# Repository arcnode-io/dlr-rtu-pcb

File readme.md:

# DLR RTU PCB 🌡️⚡

> Single-PCB CM4 carrier for a solar-powered, cellular-connected RTU — mounts to a transmission tower cross-arm, integrates SoM + cellular modem + IEEE 738 sensor suite + solar/LiFePO4 power management. Feeds [`dlr-rtu-firmware`](https://gitlab.com/arcnode-io/dlr-rtu-firmware).

Solar-powered remote terminal unit (RTU) deployed unattended on transmission tower cross-arms. A ~20W solar panel and ~50Wh LiFePO4 battery keep the CM4 running indefinitely with cellular PSM idle. A soldered Quectel BG770A (LTE Cat-M1) publishes sensor data and dynamic ratings to the MQTT broker — no site WiFi or wired backhaul required. The unit is designed for 30-year conductor-adjacent deployment with no scheduled maintenance.

~100x80mm 4-layer industrial carrier. Raspberry Pi CM4 (DF40 dual-connector) + Quectel BG770A LCC + FLIR Lepton 3.5 (SPI) + DHT22 (GPIO) + SI1145 (I2C) + YL-83 (analog via ADS1115). MPPT charger from PV input, LiFePO4 BMS, buck for 5V SoM rail, AP2112K LDO for 3.3V analog front-end. Conformal coated, IP55 when potted in field enclosure.

## System Context

```plantuml
rectangle transmission_tower {
  rectangle field_enclosure {
    rectangle dlr_carrier {
      rectangle cm4_som
      rectangle cellular_module
      rectangle sensors
      rectangle power_mgmt
    }
  }
  rectangle solar_panel
  rectangle lifepo4_battery
  rectangle conductor
}

queue mqtt_broker
rectangle dispatch_api

solar_panel -d- power_mgmt: PV input
power_mgmt -l- lifepo4_battery: charge / discharge
power_mgmt -d- cm4_som: 5V / 3V3
conductor -u- sensors: thermal view\n(FLIR Lepton)
sensors -r- cm4_som: SPI / I2C / GPIO
cm4_som -r- cellular_module: UART + USB2
cellular_module -r- mqtt_broker: LTE Cat-M1
mqtt_broker -r- dispatch_api: dynamic line rating\n(utility/dlr/...)
```

The carrier is the physical sensing + edge-compute layer of the DLR feedback loop. Every measurement flows through the IEEE 738 calculation in [`dlr-rtu-firmware`](https://gitlab.com/arcnode-io/dlr-rtu-firmware), which publishes the resulting dynamic line rating for `mock-derms-dispatch-api`'s DER curtailment trigger.

## Board Spec

```mermaid
graph LR
    SOLAR["Solar Panel<br/>~20W 12V"] --> MPPT["BQ24650 MPPT<br/>+ 2x DMN4035L"]
    MPPT --> BAT["LiFePO4 4S<br/>~50Wh + BMS"]
    BAT --> BUCK["Buck<br/>5V 3A"]
    BUCK --> CM4["CM4 SoM<br/>DF40 x2"]
    BUCK --> BG["Quectel BG770A<br/>Cat-M1 LCC"]
    BUCK --> LDO["AP2112K<br/>3.3V LDO"]
    LDO --> ADC["ADS1115<br/>I2C 0x48"]
    LDO --> UV["SI1145<br/>I2C 0x60"]
    CM4 --> FLIR["FLIR Lepton 3.5<br/>SPI0 + GPIO25"]
    CM4 --> DHT["DHT22<br/>GPIO4"]
    CM4 --> ADC
    CM4 --> UV
    ADC --> RAIN["YL-83<br/>Analog 0-3.3V"]

    style SOLAR fill:#dc4,stroke:#333
    style MPPT fill:#a94,stroke:#333
    style BAT fill:#a94,stroke:#333
    style BUCK fill:#a94,stroke:#333
    style LDO fill:#a94,stroke:#333
    style CM4 fill:#4a9,stroke:#333,color:#fff
    style BG fill:#49a,stroke:#333,color:#fff
    style FLIR fill:#49a,stroke:#333,color:#fff
    style DHT fill:#94a,stroke:#333,color:#fff
    style ADC fill:#94a,stroke:#333,color:#fff
    style UV fill:#94a,stroke:#333,color:#fff
    style RAIN fill:#669,stroke:#333,color:#fff
```

## CM4 Pinout

```mermaid
flowchart LR
classDef default fill:transparent,stroke:#333
classDef pwr fill:#4a9,stroke:#333,color:#fff
classDef spi fill:#49a,stroke:#333,color:#fff
classDef i2c fill:#94a,stroke:#333,color:#fff
classDef gpio fill:#a94,stroke:#333,color:#fff
classDef uart fill:#a49,stroke:#333,color:#fff
classDef usb fill:#669,stroke:#333,color:#fff

subgraph cm4 ["CM4 (DF40-100)"]
  p_5v["5V_IN"]
  p_sda["GPIO2 SDA1"]
  p_scl["GPIO3 SCL1"]
  p_g4["GPIO4"]
  p_g25["GPIO25"]
  p_mosi["GPIO10 MOSI"]
  p_miso["GPIO9 MISO"]
  p_sck["GPIO11 SCLK"]
  p_ce0["GPIO8 CE0"]
  p_txd["GPIO14 TXD"]
  p_rxd["GPIO15 RXD"]
  p_usb["USB2 D+/D-"]
end

subgraph onboard ["Carrier Components"]
  flir["FLIR Lepton 3.5"]
  dht["DHT22"]
  si["SI1145"]
  ads["ADS1115"]
  yl["YL-83"]
  bg["BG770A"]
end

p_mosi --> flir
p_miso --> flir
p_sck --> flir
p_ce0 --> flir
p_g25 --> flir
p_g4 --> dht
p_sda --> si
p_scl --> si
p_sda --> ads
p_scl --> ads
ads --> yl
p_txd --> bg
p_rxd --> bg
p_usb --> bg

class p_5v pwr
class p_mosi,p_miso,p_sck,p_ce0 spi
class p_sda,p_scl i2c
class p_g4,p_g25 gpio
class p_txd,p_rxd uart
class p_usb usb
```

## Sensor Interfaces

| Sensor | Interface | CM4 Pins | Sample Rate | Measurement | Feeds IEEE 738 Variable |
|--------|-----------|----------|-------------|-------------|------------------------|
| FLIR Lepton 3.5 | SPI0 + VSYNC | GPIO 8, 9, 10, 11, 25 | 8.6 Hz (frame) | Conductor surface temp | $R_{thermal}$ |
| DHT22 | GPIO4 (1-Wire) | GPIO 4 | 0.5 Hz | Ambient temp + humidity | $T_{amb}$ |
| SI1145 | I2C (0x60) | GPIO 2, 3 | 10 Hz | UV / Visible / IR irradiance | $\Delta T_{solar}$ |
| YL-83 → ADS1115 | I2C (0x48) ch0 | GPIO 2, 3 | 860 SPS | Rain intensity (0–3.3V analog) | $\Delta T_{rain}$ |

Every sensor reading on this board maps to exactly one term in the IEEE 738 dynamic rating equation:

$$ I_{max} = \sqrt{\frac{q_c + q_r - q_s}{R_{ac}}} $$

## Anemometer Variants

Single PCB + single firmware binary. Variant lives in the **kit BOM** — sensor,
cable harness, PV panel, and battery differ per SKU. Both sensors speak
NMEA 0183 (`$..MWV`) over RS-485, so the firmware driver is talker-agnostic.

### Kit BOM

| Component | High-wind kit (`DLR-CRN-HW`) | Low-wind kit (`DLR-CRN-LW`) |
|-----------|------------------------------|------------------------------|
| PCB | `dlr-rtu-pcb-v1` (same) | `dlr-rtu-pcb-v1` (same) |
| Firmware | `dlr-rtu-firmware` (same binary) | `dlr-rtu-firmware` (same binary) |
| Sensor | Calypso ULP STD | Vaisala WMT702 |
| Sensor wire protocol | NMEA `$IIMWV` over RS-485 | NMEA `$WIMWV` over RS-485 |
| Sensor accuracy (V<2 m/s) | ±5 % + 0.2 m/s offset (1 m/s threshold) | **±0.1 m/s** (0.01 m/s threshold) |
| Sensor op temp | unspecified (consumer-grade) | -10 to +60 °C |
| Cable harness | 5 m bare-wire to M12-5P | 5 m Cannon Trident 19-way to M12-5P |
| PV panel | 20 W | **30 W** |
| Battery | 50 Wh LiFePO4 | **100 Wh LiFePO4** |
| Sticker | `HW-1.0` | `LW-1.0` |
| Kit cost (approx) | ~$650 | ~$2350 |

### When to deploy which variant

Per-site SKU pick uses NREL WIND Toolkit climatology (or customer SCADA wx
history when available). Threshold: fraction-of-year with V_w < 1 m/s
perpendicular to conductor.

| Climatology | Variant | Why |
|---|---|---|
| ≤ 15 % yr V_w < 1 m/s (ridge / coastal / open plain w/ mean ≥ 6 m/s) | high-wind | uplift slice below 1 m/s is marginal; static fallback below threshold is fine |
| > 15 % yr V_w < 1 m/s (valley / sheltered / open plain w/ mean ≤ 5 m/s) | low-wind | uplift slice is material; pay $1.7 k premium to capture it |

### Fallback policy (both variants)

When the sensor reports `void` status, times out, or has a checksum/parse
error, the driver returns `None`. The IEEE 738 layer collapses None →
`V_w = 0.0` → natural-convection-only ampacity = the conductor's static
rating. Same conservative fallback used for the icing-fallback policy.

### Variant power budget

| | High-wind | Low-wind |
|---|---|---|
| Sensor continuous draw | 1 mW | 480 mW |
| System daily energy | 29.1 Wh | 40.6 Wh |
| Winter PV harvest (worst) | 45 Wh | 67.5 Wh |
| Winter margin | 1.55× | **1.66×** |
| Battery autonomy at 0 PV | 1.58 d | **2.22 d** |

Low-wind variant's 30 W / 100 Wh upgrade absorbs the WMT702's higher draw and
restores both winter margin and 2-day autonomy.

## Power Budget

| Rail | Source | Consumer | Idle (PSM) | Typical | Peak |
|------|--------|----------|------------|---------|------|
| 5V | Buck | CM4 | 80 mA | 1400 mA | 3000 mA (boot) |
| 5V | Buck | Quectel BG770A | <1 mA | 100 mA | 250 mA (TX) |
| 5V | Buck | FLIR Lepton 3.5 | 150 mA | 150 mA | 650 mA (shutter) |
| 5V | Buck | DHT22 | 1.5 mA | 1.5 mA | 2.5 mA |
| 3.3V | AP2112K LDO | ADS1115 + SI1145 + YL-83 | 9 mA | 9 mA | 14 mA |
| | | **Total @ 5V equiv** | **240 mA** | **1660 mA** | **3920 mA** |

The 3920 mA peak is a worst-case *sum*, not a supported operating point. The LMR33630 delivers 3.375 A with worst-case silicon, so a coincident CM4-boot + Lepton-shutter + modem-TX peak browns the rail out below the CM4's 4.75 V floor — firmware sequences those loads apart (**ADR-017**, derived in `theory.ipynb` §7 and asserted in `sim/test_spice.py`). The CM4 boot peak on its own holds the rail at ~4.95 V.

Daily energy with CM4-always-on idle + 1/min sensor wake + 1/15 min cellular TX: **~29 Wh/day** (derived in `theory.ipynb`). A 50 Wh battery (90% DoD) gives ~1.6 days autonomy with no PV. A 20W panel at 2.5 sun-hours/day (winter Northeast US worst case) delivers ~45 Wh/day after MPPT η — **1.55x winter margin**, 2.5x annual avg.

That margin assumes a 120 mA CM4 idle (tuned Pi OS Lite, headless). The CM4 datasheet §5.3 quotes ~400 mA typical idle; at that figure the budget is 62.6 Wh/day and the 20 W panel does **not** carry winter (0.72x). Idle current is the single measurement that most needs a bench check before committing to the panel size.

## Environmental

| Parameter | Spec | Notes |
|-----------|------|-------|
| Operating temp | -20°C to +85°C | CM4 commercial spec; cold-start heater required below -20°C |
| Conformal coat | Dow Corning 1-2577 | Applied post-assembly, mask connectors |
| Enclosure rating | IP55 (with field enclosure) | Board alone is not rated |
| Vibration | IEC 60068-2-6 (5–500 Hz, 2g) | Transmission tower wind loading |
| Expected service life | 30 years | Matches conductor replacement cycle |
| MTBF | >200,000 hours | Derated per MIL-HDBK-217F |
| Mounting | M3 standoffs, 4-corner | Single rigid PCB — no stack |

## Fabrication Pipeline

Fully scripted — no GUI step. KiCad's "Update PCB from Schematic" is GUI-only, so `cad/drawing/sync_pcb.py` does the same job from the SKiDL netlist: it rebuilds every footprint from the library and reassigns every pad net, which is what keeps the board honest about what the schematic says.

```
 1. uv run poe notebook         → theory.ipynb: power, signal integrity, 5V transients
 2. uv run poe build            → SKiDL netlist
 3. uv run poe schematic        → hierarchical .kicad_sch (one sheet per block)
 4. uv run poe validate-model   → ERC, 0 violations (exits non-zero otherwise)
 5. uv run poe sim / cover      → pytest: hand calcs + ngspice transients

 6. uv run poe layout-asm       → the whole board flow, in order:
      build       netlist from SKiDL
      sync-asm    footprints + pad nets  <- replaces the GUI "Update PCB from Schematic"
      place-asm   positions from cad/pcb_placement.yaml
      setup-asm   4-layer stack, design rules, net classes, GND + 5V planes
      fanout-asm  escape vias for the 0.4 mm connector, assigned before routing
      route-asm   Specctra DSN -> Freerouting -> SES import -> zone fill
      stitch-asm  vias from surface pads to their plane
      validate-asm DRC, 0 violations

    ┌──────────────────────────────────────────────────────┐
    │  HUMAN: review the render, adjust pcb_placement.yaml │
    └──────────────────────────────────────────────────────┘

 7. uv run poe generate-asm     → gerbers + drill + STEP + BOM + CPL
```

### Board status

ERC is 0. DRC is clean of clearance, short, annular-ring, hole and courtyard errors —
what is left is 7 silkscreen-overlap warnings and **2 open connections** out of 457
pads, both of them ground pins on J5 (Hirose DF40, 0.4 mm pitch):

| Net | Pad | At (mm) |
|---|---|---|
| GND | J5.20 | 197.80, 94.46 |
| GND | J5.25 | 199.00, 97.54 |

Both are redundant pins — the CM4 bonds its grounds internally — so what is missing is
return-path quality at that corner of the connector, not a broken net. It is still a
DRC error, so the gerbers in `output/` stay a preview until it closes.

**Why they are open.** It is a fanout-capacity limit, not a search failure. A row of
0.6 mm escape vias needs 0.75 mm centre to centre, so on a 0.4 mm pad pitch only every
other pin gets a via in the first row. The pins that miss out have to reach a second,
deeper row — but two 0.6 mm vias 0.75 mm apart leave a 0.15 mm slot, and a 0.2 mm trace
with 0.15 mm clearance needs 0.5 mm. **Once the first row is populated the second row is
unreachable.** Via rows have to be assigned before any routing happens; a router that
picks the nearest free site per pin always finishes one slot short.

`cad/drawing/fanout.py` does that assignment: it clears the connector's fanout band and
alternates along each pad row, one pin into the inter-row gap, the next out the back, so
same-side vias land 0.8 mm apart. It places all 39 escapes on J5 with zero clearance,
short or drill violations — the geometry works.

What is *not* done is the rebuild. Run on a board that is already routed, the pass has
to clear 223 tracks and vias to own its band, and `escape_pins` rebuilds only 23 of the
35 connections that leaves open — a net regression against the 2 here. Its place is
before Freerouting, where a full-strength router does the reconnection, which is where
`poe layout-asm` now calls it. **That path has not been run end to end yet**, so the
board in this repo is still the pre-fanout one. Closing the last two means either that
full regeneration, or 0.45 / 0.25 mm vias (JLCPCB advanced tier, and the 0.13 mm
annular-ring rule would have to come down with them), or six layers.

### Toolchain

**KiCad 10 required.** The board is KiCad 10 format (`20260206`); on KiCad 9
`poe validate-asm` says DRC could not run rather than passing silently. The CI
runner gets 10.x from Flatpak. The schematic is format `20250114`, which both
versions read.

ERC is a blocking gate in CI. DRC runs and reports but does not gate yet — the two
open ground pins above are real errors; the `|| echo` comes off once they are closed.

## Layer Stack

4-layer, 1.6 mm FR4, controlled impedance (ADR-016). Applied by `cad/drawing/board_setup.py`, so a regenerated board always has the same stack.

| Layer | Use |
|-------|-----|
| F.Cu | Signal — high-speed (SPI 20MHz, USB2.0 to BG770A) |
| In1.Cu | GND plane, unbroken (reference for the USB pair and the Lepton SPI) |
| In2.Cu | 5V_RAIL plane — CM4, both LDOs and the Lepton feed off it via drops |
| B.Cu | Signal — low-speed (I2C, GPIO, UART) |

Signals are confined to F.Cu / B.Cu: the router is told the inner layers are `power` type, so nothing slices a plane. VBAT, 3V3 and 3V8 run as 0.6 mm traces (`power` net class), necked to 0.25/0.2 mm where an escape has to squeeze past a 0.4 mm-pitch pad. Every via is 0.6/0.3 mm: a 0.5/0.25 mm via would ease the DF40 fanout but leaves a 0.125 mm annular ring, under the 0.13 mm rule.

Unbroken ground plane under the Lepton is critical — SPI runs at 20 MHz and the thermal imager is noise-sensitive. USB2.0 to the BG770A is differential-routed at 90Ω matched impedance with GND directly below. Analog traces from YL-83 to ADS1115 are guard-ringed on F.Cu. Cellular antenna is 50Ω microstrip to a u.FL connector.

## Project Structure

```
├── pyproject.toml              # Dependencies and build config
├── theory.ipynb                # Power, signal integrity, 5V transient derivations
├── sim/
│   ├── constants.py            # Sourced part parameters (datasheet + edition cited)
│   ├── model.py                # Closed-form: buck current, energy, I2C/SPI/USB
│   ├── spice_bank.py           # Shared 5V output capacitor bank
│   ├── spice_ripple.py         # ngspice: open-loop switching ripple (Eq 7)
│   ├── spice_load_step.py      # ngspice: averaged current-mode boot-peak droop
│   ├── test_run.py             # Assert closed-form results match theory.ipynb
│   └── test_spice.py           # Assert ngspice results match theory.ipynb §7
├── cad/
│   ├── netlist/
│   │   ├── model.py            # Top-level SKiDL circuit (main carrier)
│   │   ├── charger.py          # Solar input + BQ24650 MPPT charger (ADR-015)
│   │   ├── power.py            # LMR33630 5V buck + AP2112K / LP5907 LDOs
│   │   ├── som.py              # CM4 DF40 connector + decoupling
│   │   ├── cellular.py         # BG770A + SIM holder + u.FL
│   │   ├── sensors.py          # FLIR (FFC), DHT22, SI1145, ADS1115, YL-83
│   │   ├── anemometer.py       # RS-485 wind sensor port (SKU-agnostic)
│   │   ├── connectors.py       # Battery + debug + USB-C commissioning
│   │   └── lepton_daughter.py  # Daughterboard SKiDL (Molex socket + FFC)
│   ├── schematic/              # Hierarchical .kicad_sch generator
│   │   ├── schematic.py        # Netlist parse, block classification, placement
│   │   ├── multi_sheet.py      # Per-block child sheets, power symbols, PWR_FLAG
│   │   ├── root_sheet.py       # Root sheet + cross-net sheet pins
│   │   └── sch_guard.py        # Fails the build on cross-net wire/pin collisions
│   ├── drawing/                # Board pipeline (system python3 — pcbnew)
│   │   ├── sync_pcb.py         # Footprints + pad nets from the netlist
│   │   ├── place_pcb.py        # Positions from pcb_placement.yaml
│   │   ├── board_setup.py      # 4-layer stack, rules, net classes, planes
│   │   ├── route_pcb.py        # DSN -> Freerouting -> SES -> fill
│   │   ├── fanout.py           # Pre-assigned escape vias for fine-pitch connectors
│   │   ├── stitch_planes.py    # Surface-pad vias into the planes
│   │   ├── close_gaps.py       # L-shaped hops across the autorouter's leftovers
│   │   ├── maze_grid.py        # Grid window shared by the escape router
│   │   ├── maze_field.py       # Analytic clearance fields (foreign copper only)
│   │   ├── maze_search.py      # Grid A*, 8-way, with via layer changes
│   │   ├── maze_escape.py      # Route + verify one connection, or tear it out again
│   │   ├── escape_pins.py      # Drives the escape router off the DRC report
│   │   ├── rip_targets.py      # Finds a stranded pin's blockers; performs the rip
│   │   └── rip_up.py           # Rip / re-route / keep-only-if-better loop
│   ├── lepton_daughter/        # Second PCB (per ADR-013) — Lepton + bracket
│   ├── assembly/               # CadQuery → GLB pipeline (build_assembly.py)
│   ├── layout_spec.yaml        # Schematic block layout
│   ├── pcb_placement.yaml      # Main-PCB component positions
│   └── drawing-sheet.kicad_wks # Title block
├── output/
│   ├── drawings/               # Schematic SVG + PDF
│   ├── gerbers/                # Fabrication files
│   └── fab/                    # BOM + CPL for assembly
└── readme.md                   # This file
```

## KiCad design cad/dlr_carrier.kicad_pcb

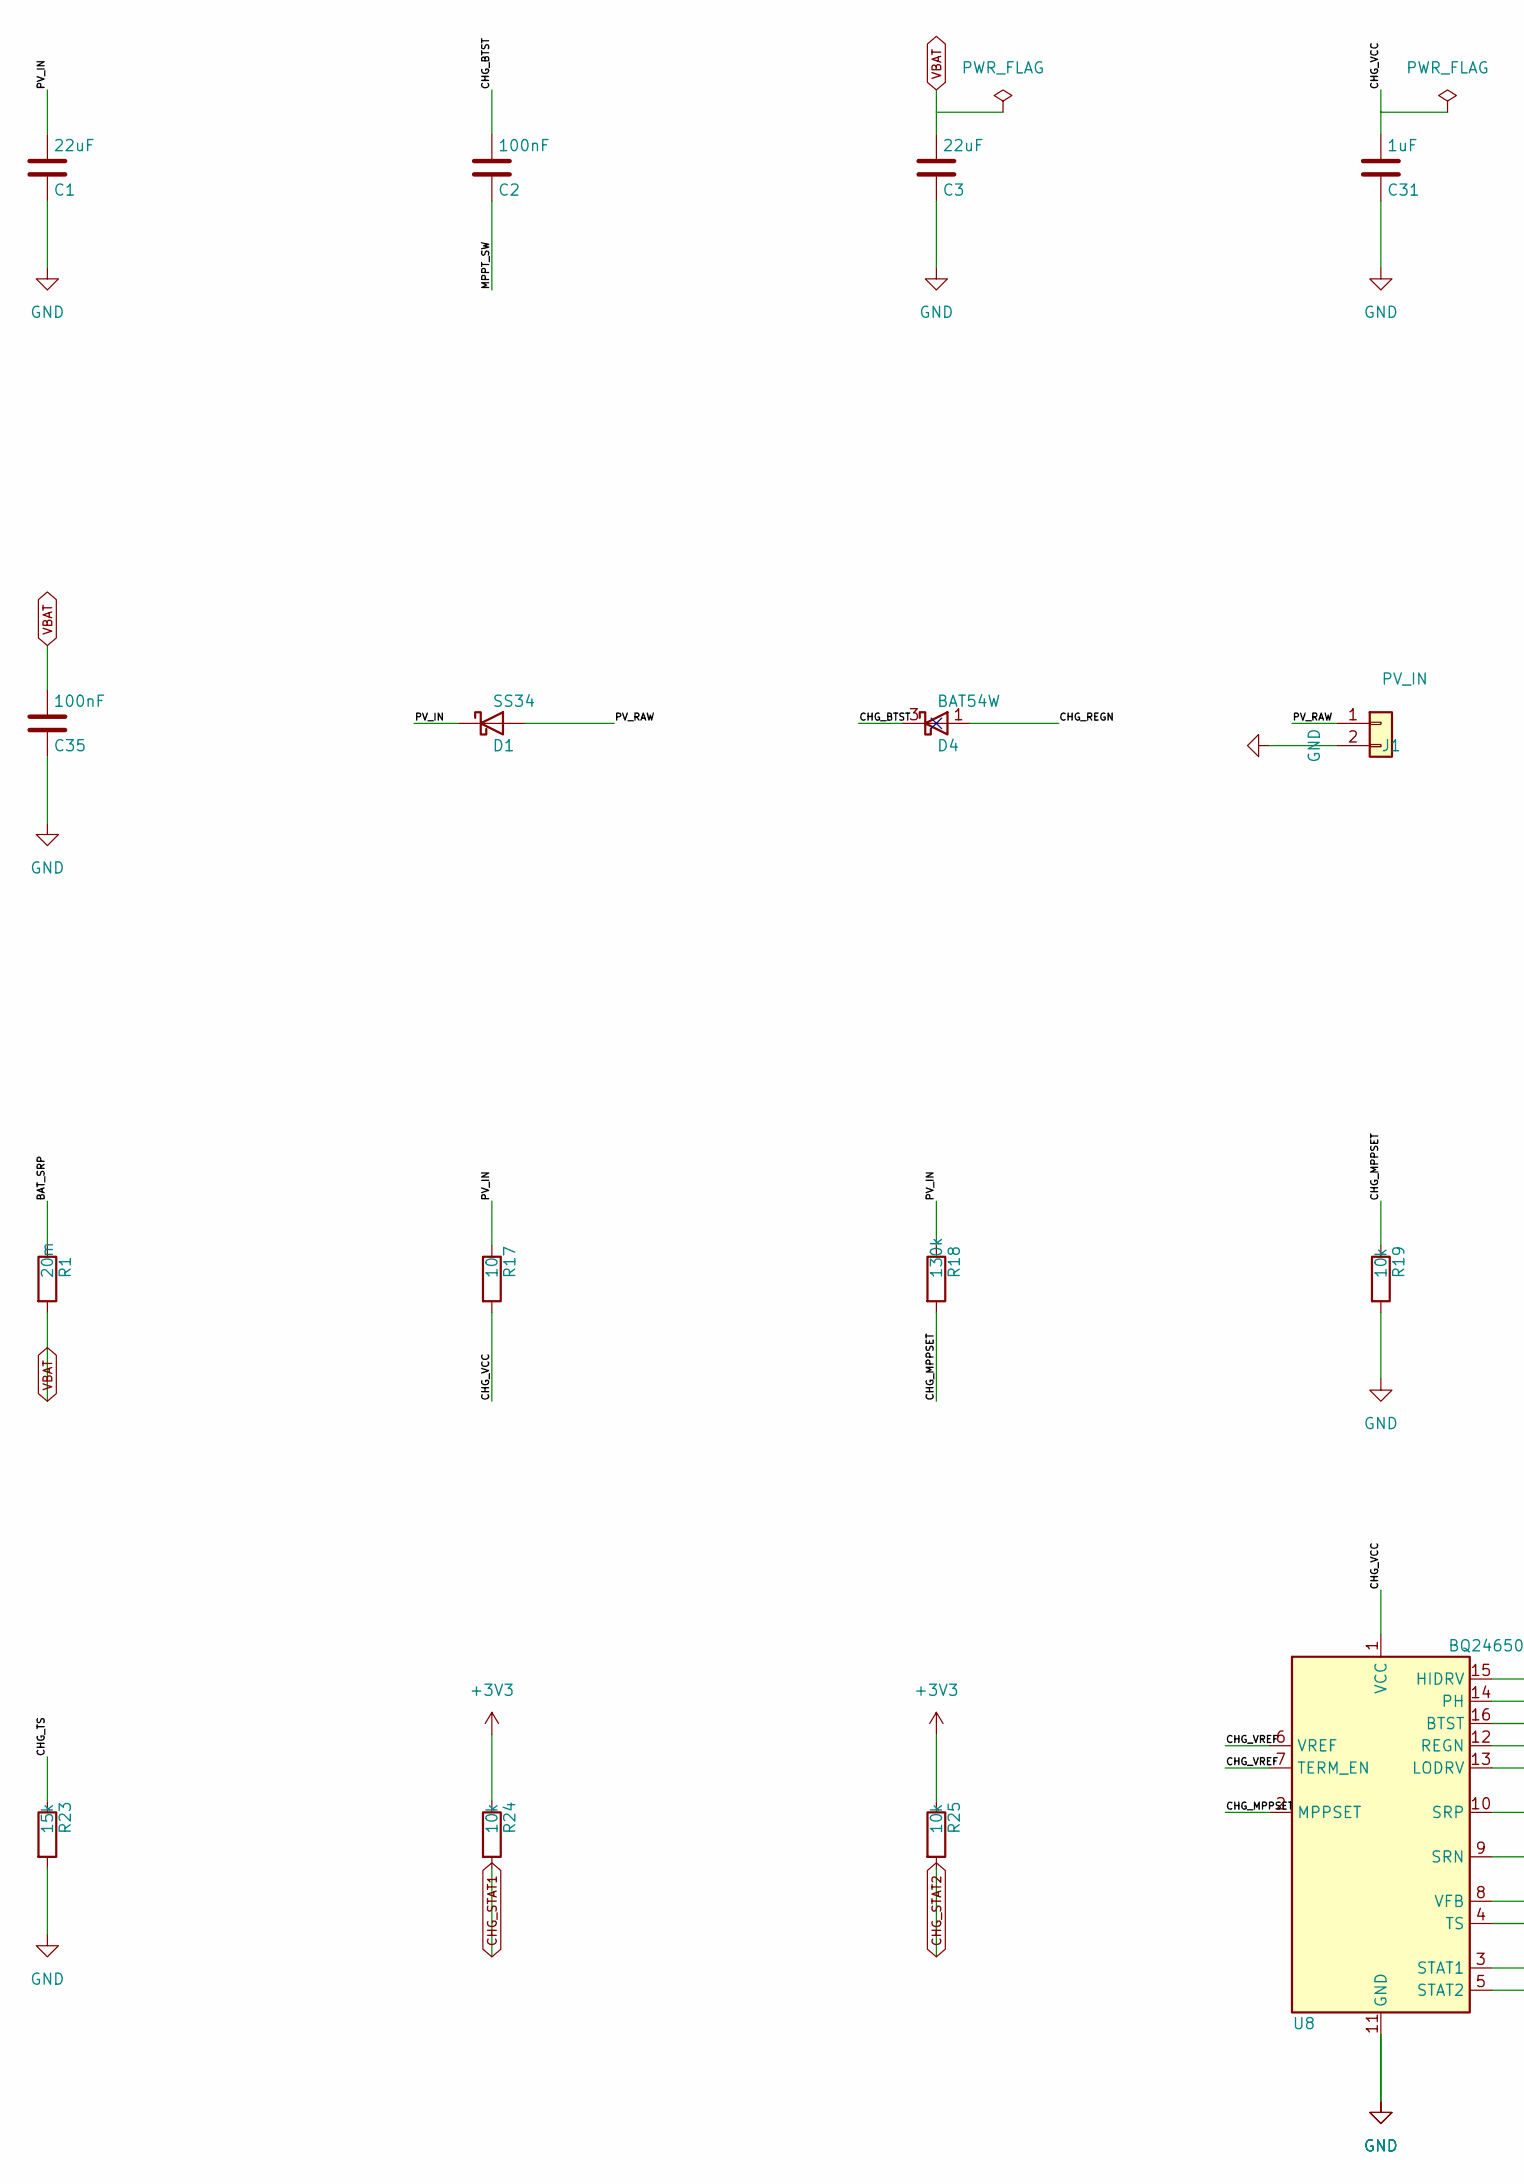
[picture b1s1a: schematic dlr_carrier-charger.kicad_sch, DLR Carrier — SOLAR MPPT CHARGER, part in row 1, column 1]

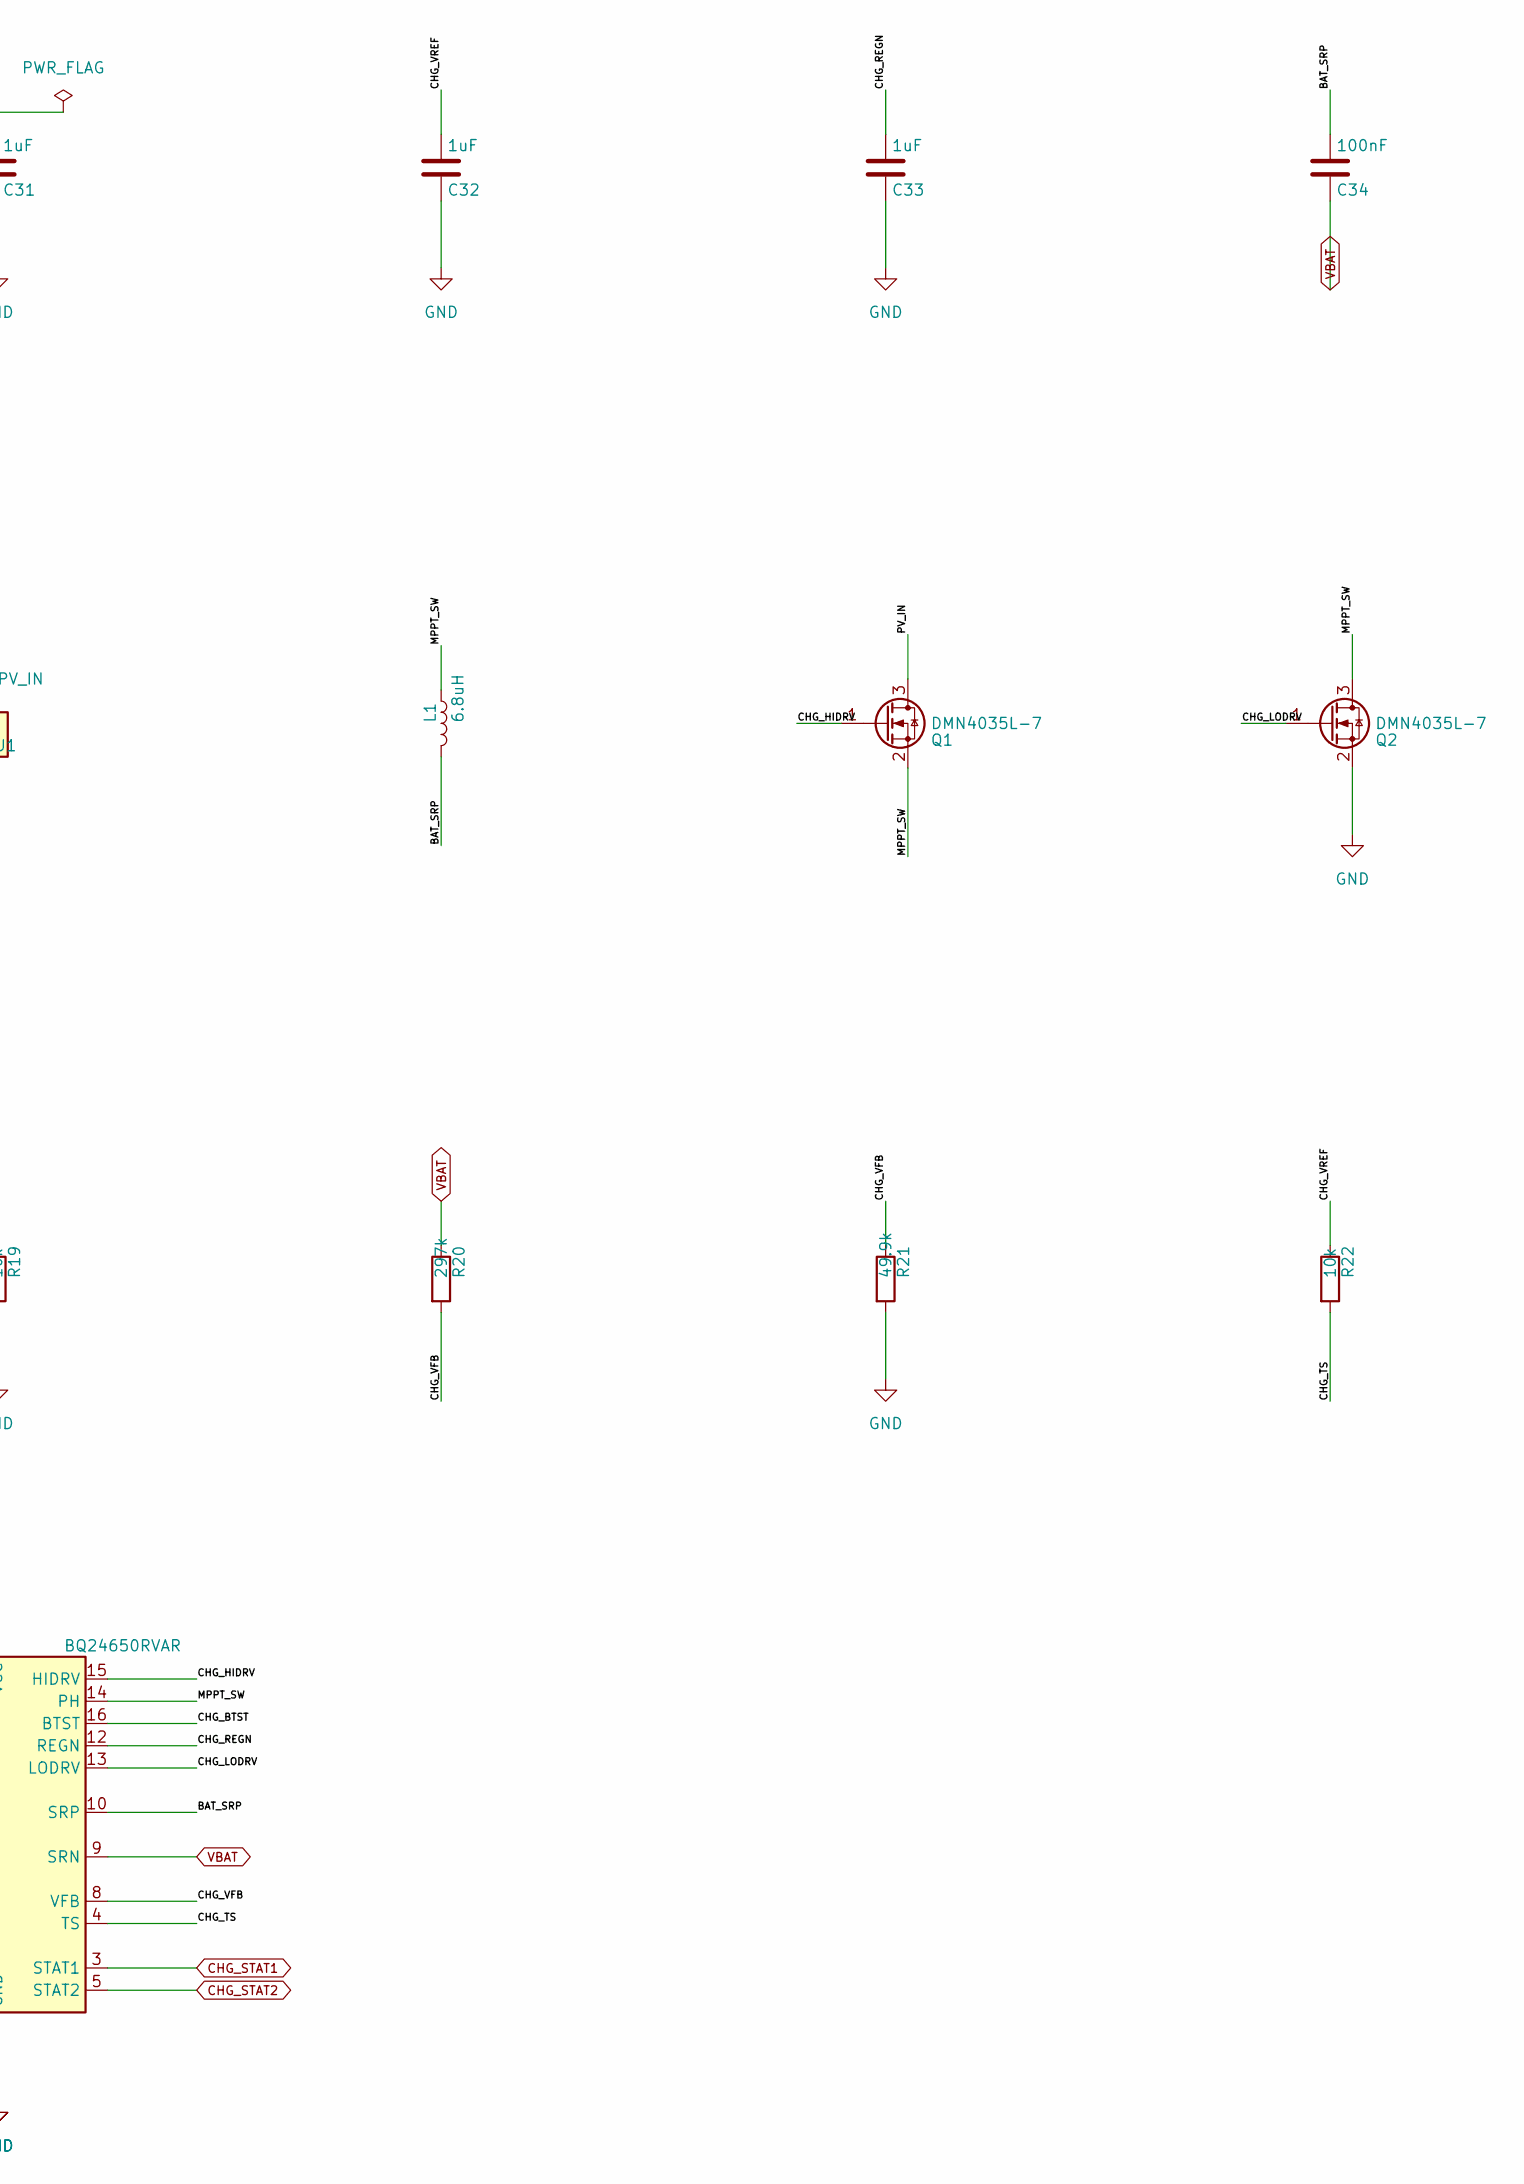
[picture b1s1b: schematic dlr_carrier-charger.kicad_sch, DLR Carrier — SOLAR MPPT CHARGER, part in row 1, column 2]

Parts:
C1, C3: 22uF; C_1206_3216Metric
C2, C34, C35: 100nF; C_0402_1005Metric
C31, C32, C33: 1uF; C_0402_1005Metric
D1: SS34; D_SMA
D4: BAT54W; SOT-323_SC-70
J1: PV_IN; TerminalBlock_Phoenix_MKDS-1,5-2-5.08_1x02_P5.08mm_Horizont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
L1: 6.8uH; L_Bourns_SRN8040TA
Q1, Q2: DMN4035L-7; SOT-23
R1: 20m; R_1206_3216Metric
R17: 10; R_0402_1005Metric
R18: 130k; R_0402_1005Metric
R19, R22, R24, R25: 10k; R_0402_1005Metric
R20: 297k; R_0402_1005Metric
R21: 49.9k; R_0402_1005Metric
R23: 15k; R_0402_1005Metric
U8: BQ24650RVAR; Texas_RVA_VQFN-16-1EP_3.5x3.5mm_P0.5mm_EP2.14x2.14mm_Therma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

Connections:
3V3: R24.1, R25.1; also elsewhere on the board
BAT_SRP: C34.1, L1.2, R1.1, U8.10 (SRP)
CHG_BTST: C2.1, D4.3 (K), U8.16 (BTST)
CHG_HIDRV: Q1.1 (G), U8.15 (HIDRV)
CHG_LODRV: Q2.1 (G), U8.13 (LODRV)
CHG_MPPSET: R18.2, R19.1, U8.2 (MPPSET)
CHG_REGN: C33.1, D4.1 (A), U8.12 (REGN)
CHG_STAT1: R24.2, U8.3 (STAT1); also elsewhere on the board
CHG_STAT2: R25.2, U8.5 (STAT2); also elsewhere on the board
CHG_TS: R22.2, R23.1, U8.4 (TS)
CHG_VCC: C31.1, R17.2, U8.1 (VCC)
CHG_VFB: R20.2, R21.1, U8.8 (VFB)
CHG_VREF: C32.1, R22.1, U8.6 (VREF), U8.7 (TERM_EN)
GND: C1.2, C3.2, C31.2, C32.2, C33.2, C35.2, J1.2, Q2.2 (S), R19.2, R21.2, R23.2, U8.11 (GND), U8.17 (GND); also elsewhere on the board
MPPT_SW: C2.2, L1.1, Q1.2 (S), Q2.3 (D), U8.14 (PH)
PV_IN: C1.1, D1.1 (K), Q1.3 (D), R17.1, R18.1
PV_RAW: D1.2 (A), J1.1
VBAT: C3.1, C34.2, C35.1, R1.2, R20.1, U8.9 (SRN); also elsewhere on the board

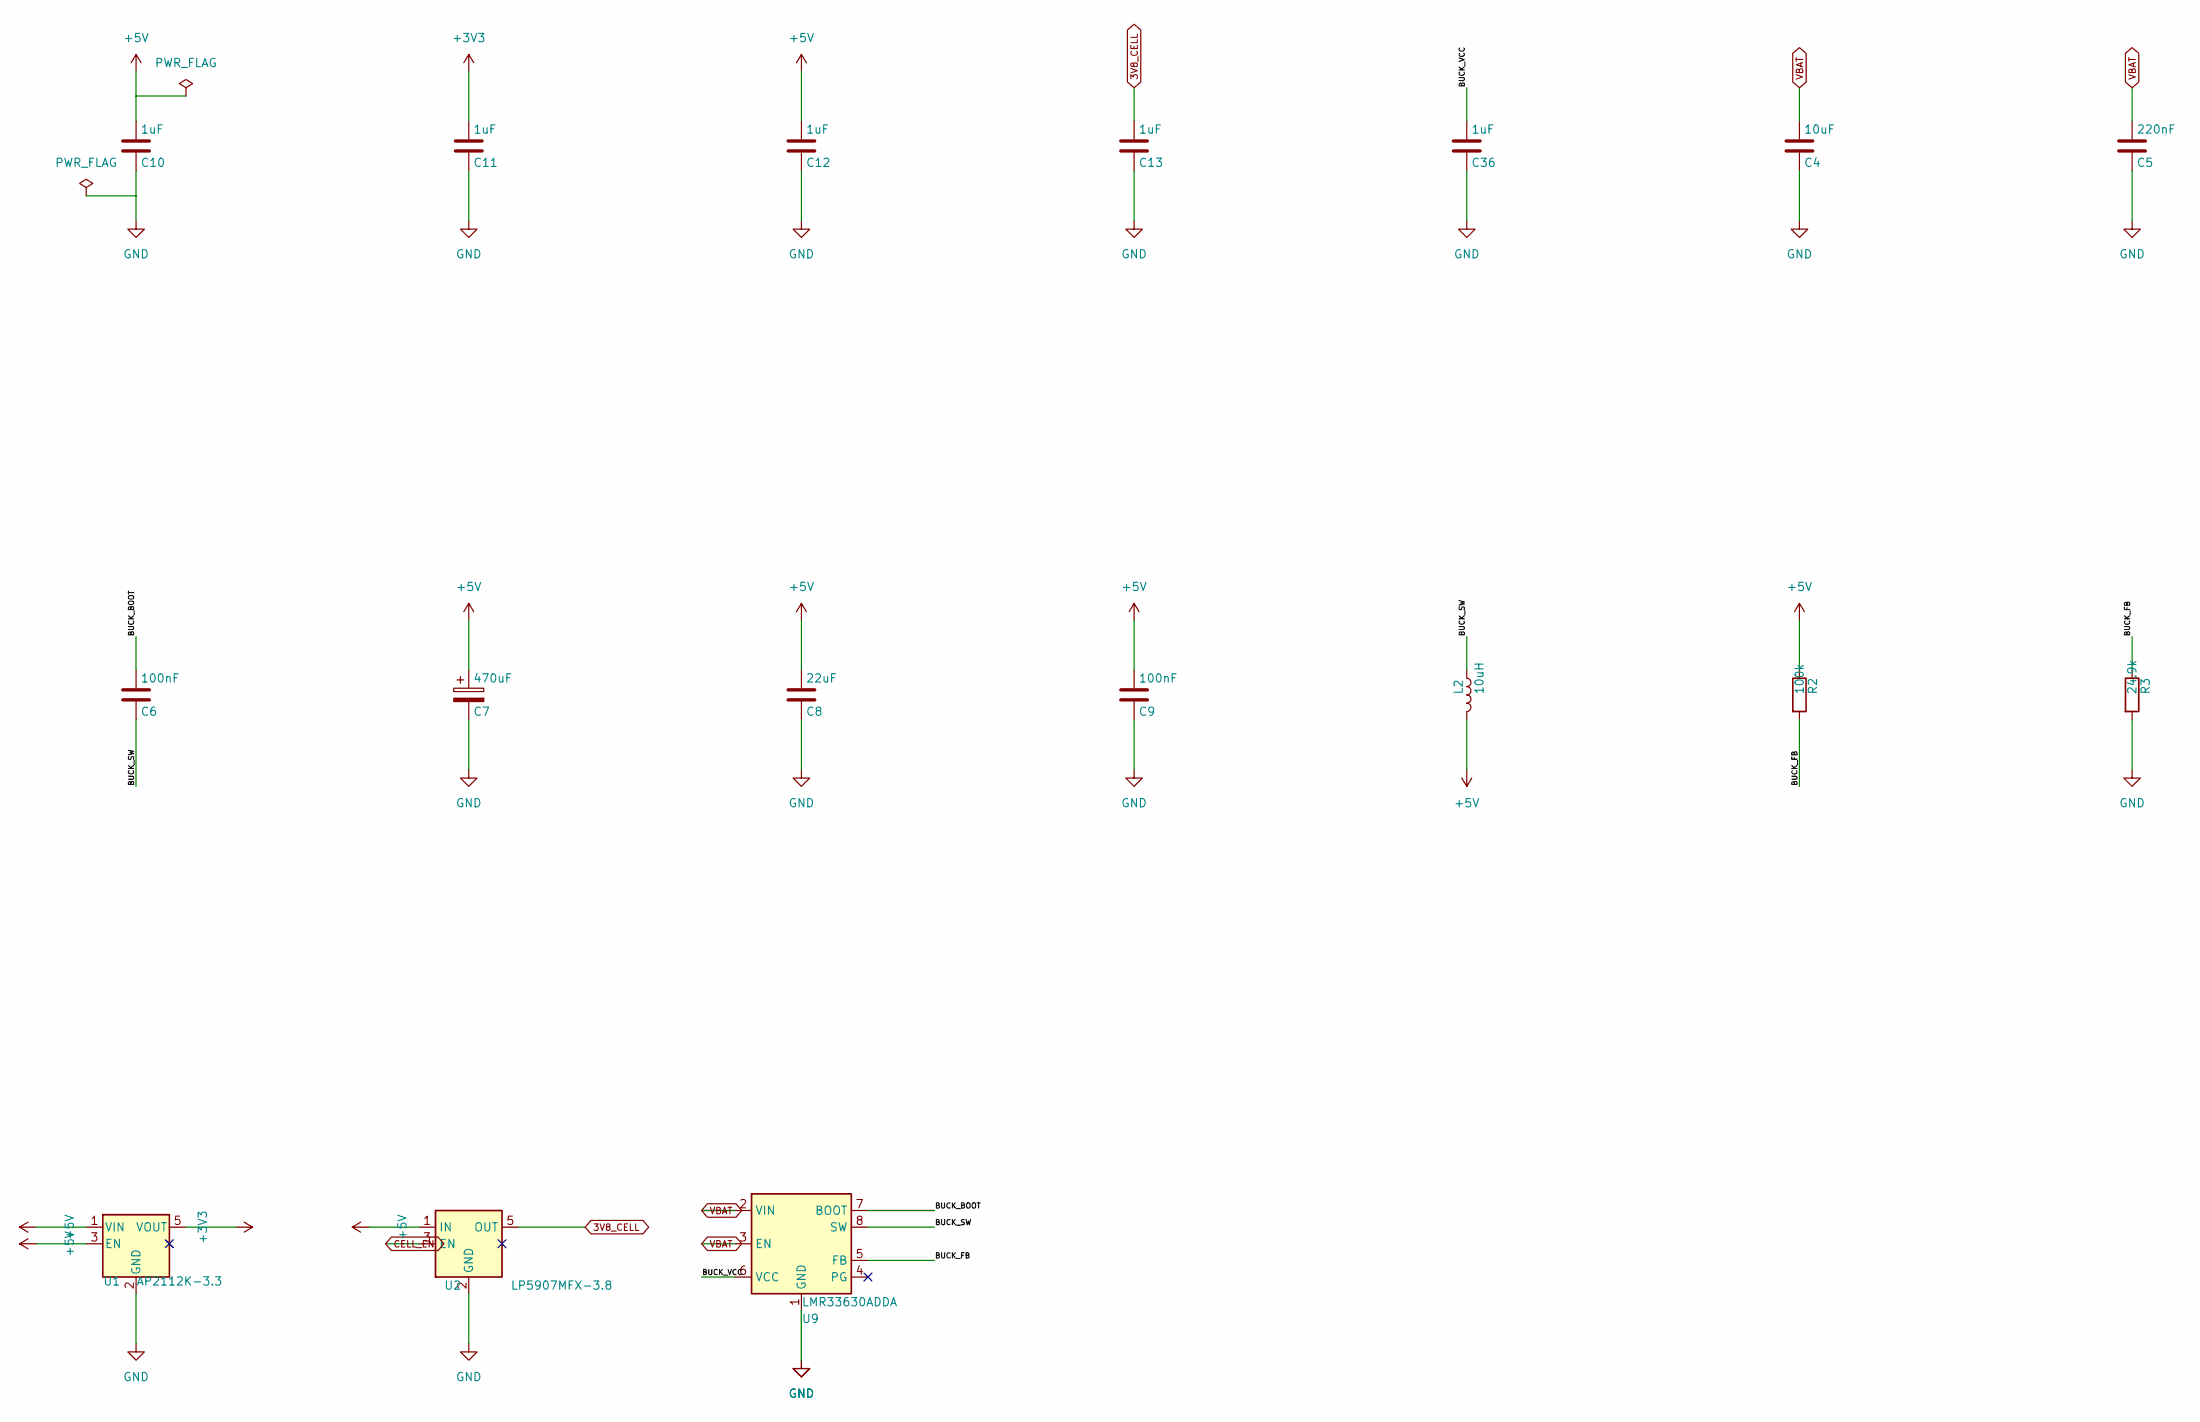
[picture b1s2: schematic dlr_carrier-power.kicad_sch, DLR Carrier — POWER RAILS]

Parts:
C4: 10uF; C_1206_3216Metric
C5: 220nF; C_0402_1005Metric
C6, C9: 100nF; C_0402_1005Metric
C7: 470uF; CP_Elec_8x10
C8: 22uF; C_0805_2012Metric
C10, C11, C12, C13, C36: 1uF; C_0402_1005Metric
L2: 10uH; L_Bourns_SRN8040TA
R2: 100k; R_0402_1005Metric
R3: 24.9k; R_0402_1005Metric
U1: AP2112K-3.3; SOT-23-5
U2: LP5907MFX-3.8; SOT-23-5
U9: LMR33630ADDA; Texas_HSOP-8-1EP_3.9x4.9mm_P1.27mm_ThermalVias

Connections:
3V3: C11.1, U1.5 (VOUT); also elsewhere on the board
3V8_CELL: C13.1, U2.5 (OUT); also elsewhere on the board
5V_RAIL: C7.1, C8.1, C9.1, C10.1, C12.1, L2.2, R2.1, U1.1 (VIN), U1.3 (EN), U2.1 (IN); also elsewhere on the board
BUCK_BOOT: C6.1, U9.7 (BOOT)
BUCK_FB: R2.2, R3.1, U9.5 (FB)
BUCK_SW: C6.2, L2.1, U9.8 (SW)
BUCK_VCC: C36.1, U9.6 (VCC)
CELL_EN: U2.3 (EN); also elsewhere on the board
GND: C4.2, C5.2, C7.2, C8.2, C9.2, C10.2, C11.2, C12.2, C13.2, C36.2, R3.2, U1.2 (GND), U2.2 (GND), U9.1 (GND), U9.9 (GND); also elsewhere on the board
VBAT: C4.1, C5.1, U9.2 (VIN), U9.3 (EN); also elsewhere on the board

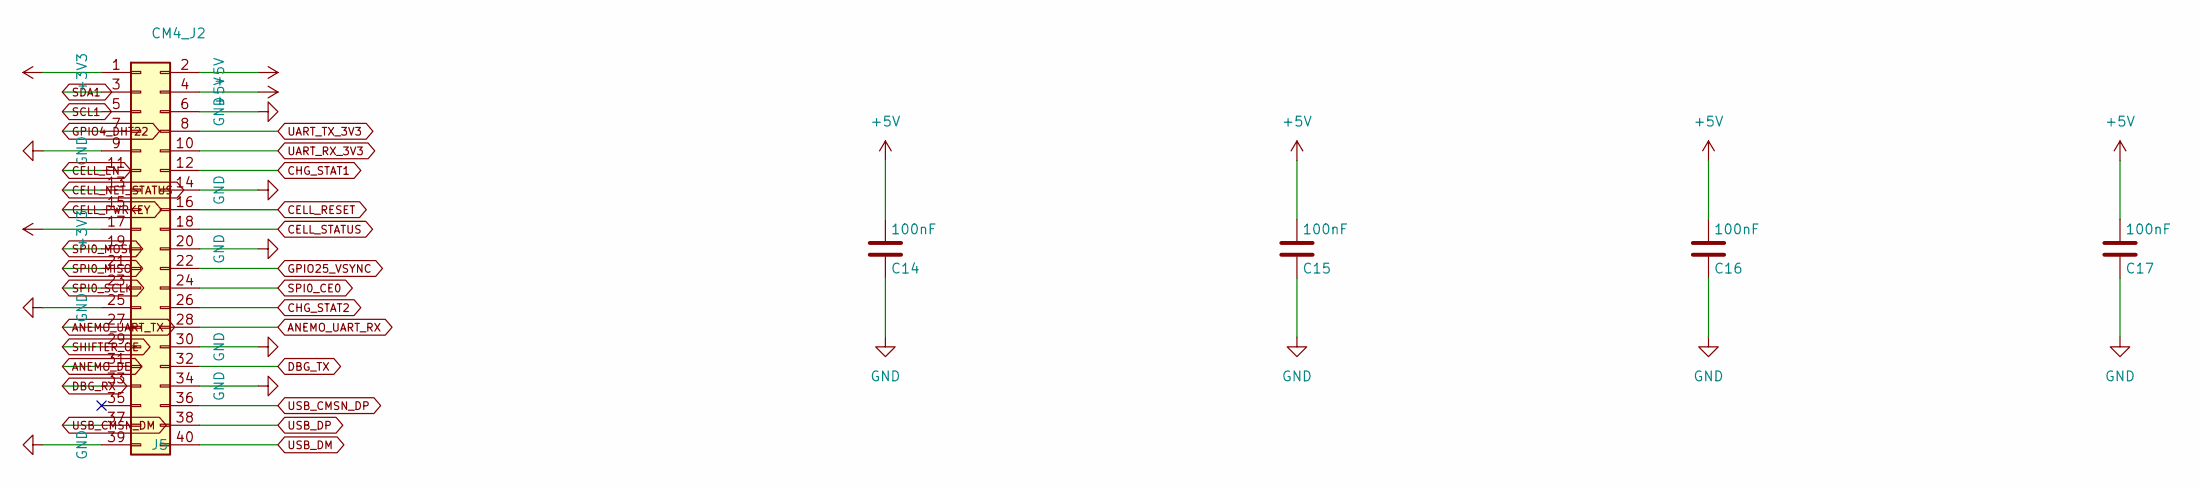
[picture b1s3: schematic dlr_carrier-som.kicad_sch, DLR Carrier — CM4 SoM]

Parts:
C14, C15, C16, C17: 100nF; C_0402_1005Metric
J5: CM4_J2; Hirose_DF40HC(3.0)-40DS-0.4V_2x20_P0.4mm

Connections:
3V3: J5.1, J5.17; also elsewhere on the board
5V_RAIL: C14.1, C15.1, C16.1, C17.1, J5.2, J5.4; also elsewhere on the board
ANEMO_DE: J5.31; also elsewhere on the board
ANEMO_UART_RX: J5.28; also elsewhere on the board
ANEMO_UART_TX: J5.27; also elsewhere on the board
CELL_EN: J5.11; also elsewhere on the board
CELL_NET_STATUS: J5.13; also elsewhere on the board
CELL_PWRKEY: J5.15; also elsewhere on the board
CELL_RESET: J5.16; also elsewhere on the board
CELL_STATUS: J5.18; also elsewhere on the board
CHG_STAT1: J5.12; also elsewhere on the board
CHG_STAT2: J5.26; also elsewhere on the board
DBG_RX: J5.33; also elsewhere on the board
DBG_TX: J5.32; also elsewhere on the board
GND: C14.2, C15.2, C16.2, C17.2, J5.6, J5.9, J5.14, J5.20, J5.25, J5.30, J5.34, J5.39; also elsewhere on the board
GPIO4_DHT22: J5.7; also elsewhere on the board
GPIO25_VSYNC: J5.22; also elsewhere on the board
SCL1: J5.5; also elsewhere on the board
SDA1: J5.3; also elsewhere on the board
SHIFTER_OE: J5.29; also elsewhere on the board
SPI0_CE0: J5.24; also elsewhere on the board
SPI0_MISO: J5.21; also elsewhere on the board
SPI0_MOSI: J5.19; also elsewhere on the board
SPI0_SCLK: J5.23; also elsewhere on the board
UART_RX_3V3: J5.10; also elsewhere on the board
UART_TX_3V3: J5.8; also elsewhere on the board
USB_CMSN_DM: J5.37; also elsewhere on the board
USB_CMSN_DP: J5.36; also elsewhere on the board
USB_DM: J5.40; also elsewhere on the board
USB_DP: J5.38; also elsewhere on the board

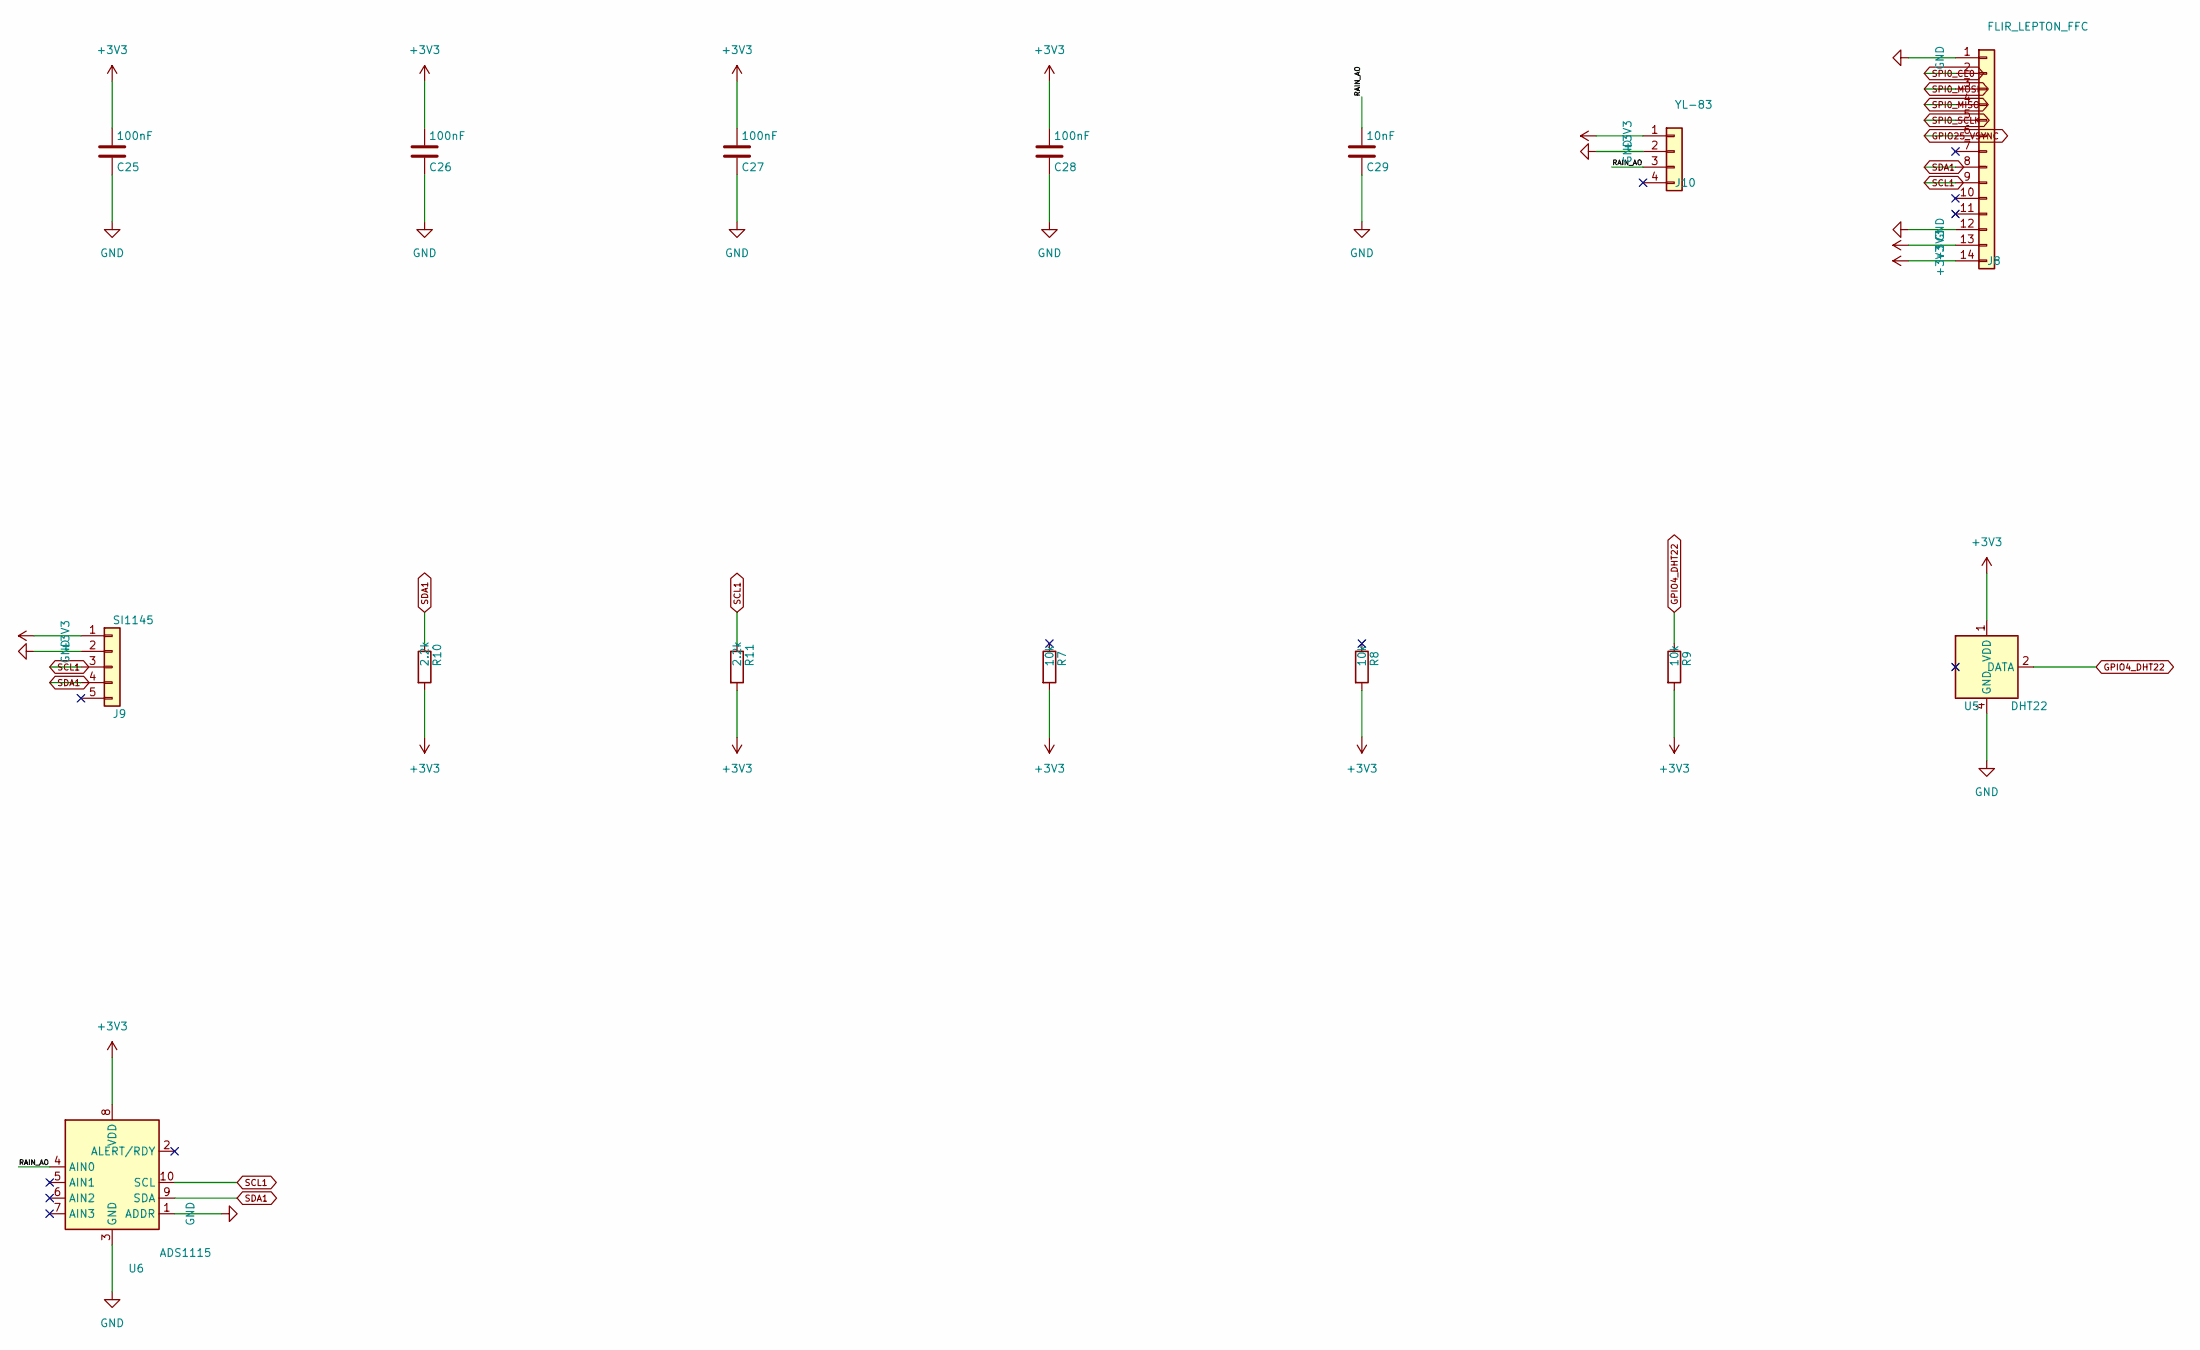
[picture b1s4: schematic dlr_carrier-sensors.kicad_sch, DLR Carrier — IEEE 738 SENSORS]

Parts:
C25, C26, C27, C28: 100nF; C_0402_1005Metric
C29: 10nF; C_0402_1005Metric
J8: FLIR_LEPTON_FFC; Hirose_FH12-14S-0.5SH_1x14-1MP_P0.50mm_Horizontal
J9: SI1145; PinHeader_1x05_P2.54mm_Vertical
J10: YL-83; PinHeader_1x04_P2.54mm_Vertical
R7, R8, R9: 10k; R_0402_1005Metric
R10, R11: 2.2k; R_0402_1005Metric
U5: DHT22; Aosong_DHT11_5.5x12.0_P2.54mm
U6: ADS1115; MSOP-10_3x3mm_P0.5mm

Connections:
3V3: C25.1, C26.1, C27.1, C28.1, J8.13, J8.14, J9.1, J10.1, R7.2, R8.2, R9.2, R10.2, R11.2, U5.1 (VDD), U6.8 (VDD); also elsewhere on the board
GND: C25.2, C26.2, C27.2, C28.2, C29.2, J8.1, J8.12, J9.2, J10.2, U5.4 (GND), U6.1 (ADDR), U6.3 (GND); also elsewhere on the board
GPIO4_DHT22: R9.1, U5.2 (DATA); also elsewhere on the board
GPIO25_VSYNC: J8.6; also elsewhere on the board
unnamed: J8.10, R7.1
unnamed: J8.11, R8.1
RAIN_AO: C29.1, J10.3, U6.4 (AIN0)
SCL1: J8.9, J9.3, R11.1, U6.10 (SCL); also elsewhere on the board
SDA1: J8.8, J9.4, R10.1, U6.9 (SDA); also elsewhere on the board
SPI0_CE0: J8.2; also elsewhere on the board
SPI0_MISO: J8.4; also elsewhere on the board
SPI0_MOSI: J8.3; also elsewhere on the board
SPI0_SCLK: J8.5; also elsewhere on the board
